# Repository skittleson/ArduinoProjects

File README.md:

# Arduino Projects

## Resources

https://arduino-esp8266.readthedocs.io/en/latest/exception_causes.html

Use a symbolic link to share common connectivity set of logic
`mklink /H "C:\Dev\ArduinoProjects\Sprinkler\_autoConnectLocal.ino" "C:\Dev\ArduinoProjects\AutoConnectLocal\_autoConnectLocal.ino"`

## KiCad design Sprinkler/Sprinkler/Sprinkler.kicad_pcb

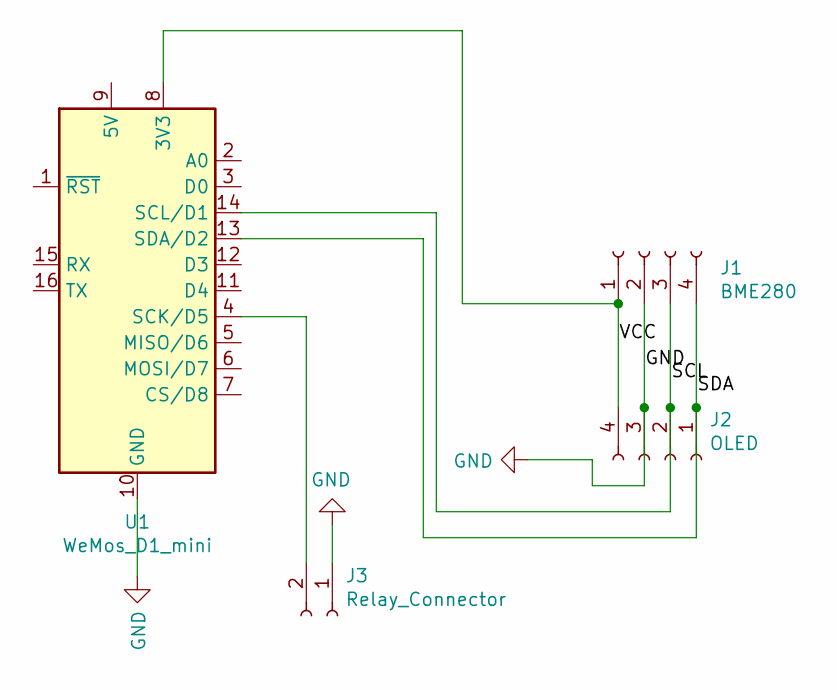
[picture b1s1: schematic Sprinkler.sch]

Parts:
J1: BME280; PinHeader_1x04_P2.54mm_Vertical
J2: OLED; PinHeader_1x04_P2.54mm_Vertical
J3: Relay_Connector; PinHeader_1x02_P2.54mm_Vertical
U1: WeMos_D1_mini; WEMOS_D1_mini_light

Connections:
/SCL: J1.3, J2.2, U1.14 (SCL/D1)
/SDA: J1.4, J2.1, U1.13 (SDA/D2)
/VCC: J1.1, J2.4, U1.8 (3V3)
GND: J1.2, J2.3, J3.1, U1.10 (GND)
unnamed: J3.2, U1.4 (SCK/D5)

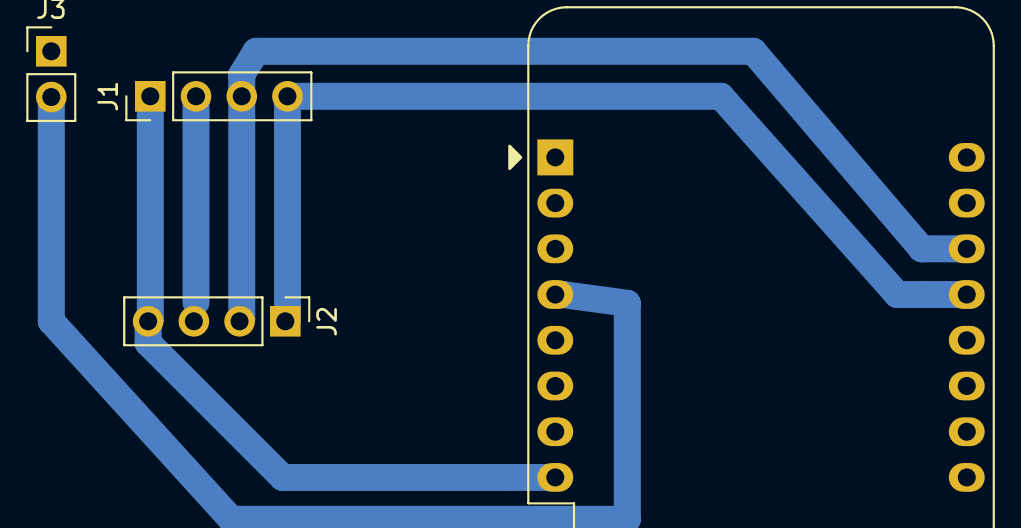
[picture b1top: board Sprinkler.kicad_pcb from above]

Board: 2 copper layers, 4 parts (0 on the bottom side), 5 nets.

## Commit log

2020-03-15 power monitor projects
2020-03-16 bugs resolved for power switch monitor
2020-03-16 ignore correct files
2020-03-23 stablize publish messages
2020-03-24 Sprinkler controller mvp
2020-04-18 Improvements and stablize
2020-04-28 project updates
2020-05-06 Sprinkler and acl
2020-05-07 OTA and Sprinkler relay state publishing
2020-05-25 Sprinkler stablize updates
2020-05-26 Defer mqtt callback processing to acl loop
2020-05-26 Remove restrictions on data uploading and bme collection
2020-06-10 use a ino for auto connect local. Update power switch monitor and sprinkler
